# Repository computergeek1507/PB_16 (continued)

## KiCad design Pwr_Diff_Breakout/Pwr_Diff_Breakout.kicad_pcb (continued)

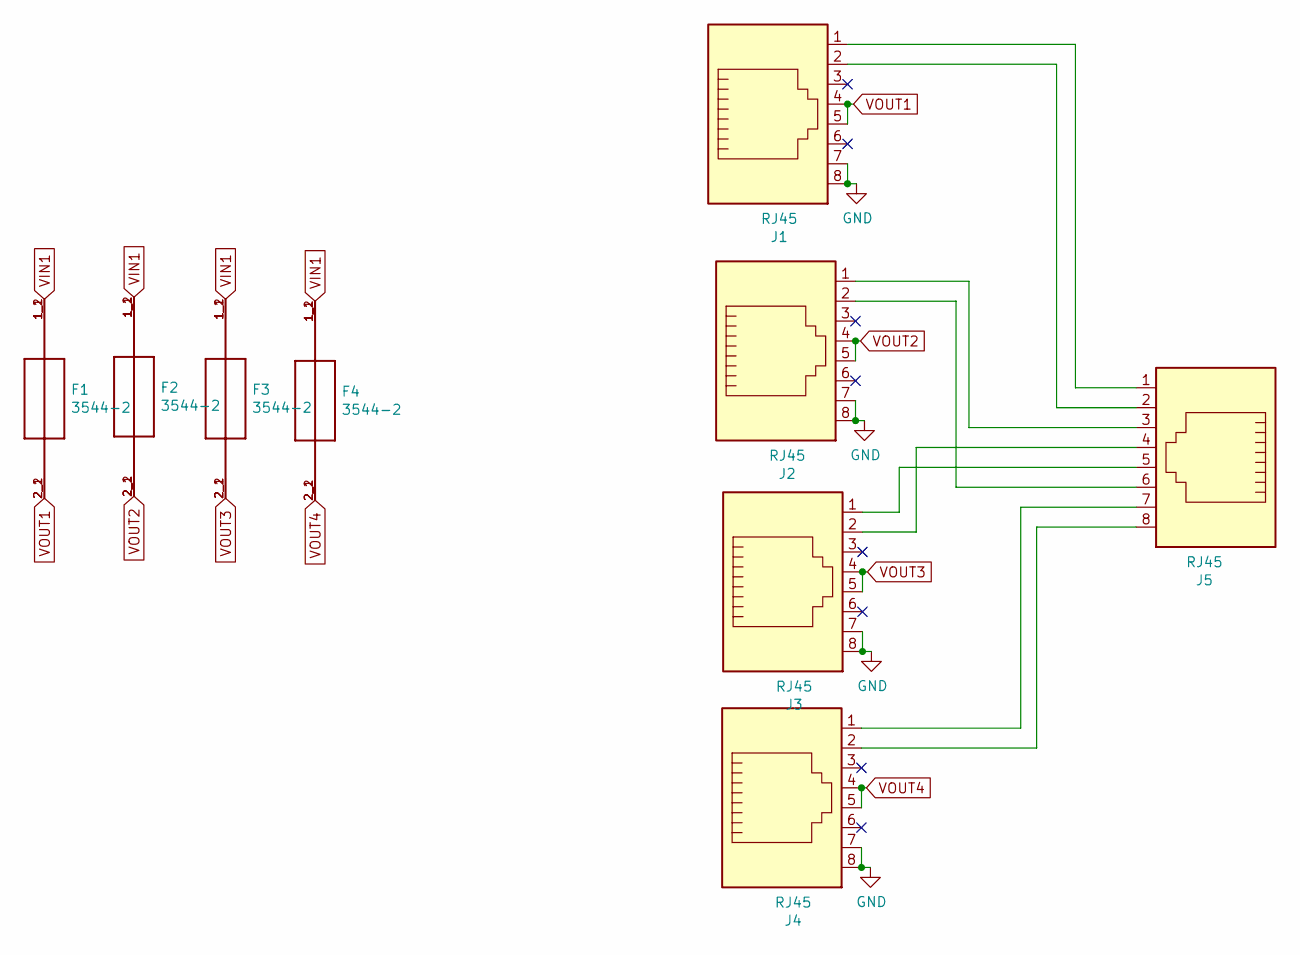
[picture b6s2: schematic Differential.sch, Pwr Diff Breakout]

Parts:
F1, F2, F3, F4: 3544-2; FUSE_3544-2; MPN 3544-2; Digi-Key_PN 36-3544-2-ND
J1, J2, J3, J4, J5: RJ45; RJ45_Amphenol_54602-x08_Horizontal; MPN A-2014-2-4-R; Digi-Key_PN AE10392-ND

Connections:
GND: J1.7, J1.8, J2.7, J2.8, J3.7, J3.8, J4.7, J4.8; also elsewhere on the board
unnamed: J1.1, J5.1
unnamed: J1.2, J5.2
unnamed: J2.1, J5.3
unnamed: J2.2, J5.6
unnamed: J3.1, J5.5
unnamed: J3.2, J5.4
unnamed: J4.1, J5.7
unnamed: J4.2, J5.8
VIN1: F1.1_1 (1), F1.1_2 (1), F2.1_1 (1), F2.1_2 (1), F3.1_1 (1), F3.1_2 (1), F4.1_1 (1), F4.1_2 (1); also elsewhere on the board
VOUT1: F1.2_1 (2), F1.2_2 (2), J1.4, J1.5
VOUT2: F2.2_1 (2), F2.2_2 (2), J2.4, J2.5
VOUT3: F3.2_1 (2), F3.2_2 (2), J3.4, J3.5
VOUT4: F4.2_1 (2), F4.2_2 (2), J4.4, J4.5

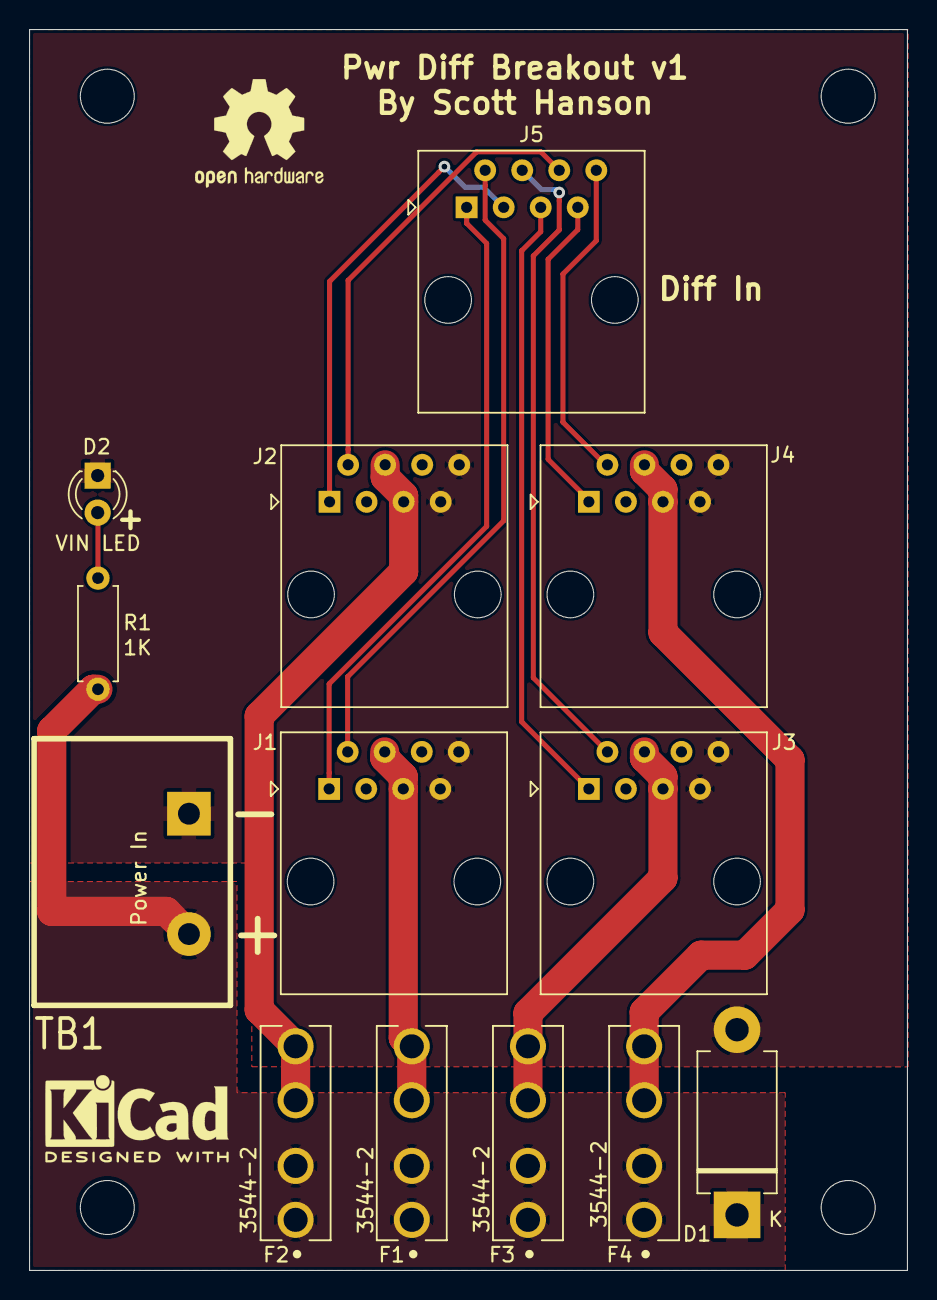
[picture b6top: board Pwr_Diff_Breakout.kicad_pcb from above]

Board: 2 copper layers, 60.2 x 85.1 mm, 13 parts (0 on the bottom side), 15 nets.

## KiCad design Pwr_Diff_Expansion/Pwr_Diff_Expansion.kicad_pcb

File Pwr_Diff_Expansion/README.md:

# Copyright and Disclaimer
Copyright: Scott Hanson

This documentation describes Open Hardware and is licensed under the CERN Open Hardware License Version 2 - Strongly Reciprocal. (CERN-OHL-S)

You may redistribute and modify this documentation under the terms of the CERN OHL-S-v2 (https://ohwr.org/cern_ohl_s_v2.txt). This documentation is distributed WITHOUT ANY EXPRESS OR IMPLIED WARRANTY, INCLUDING OF MERCHANTABILITY, SATISFACTORY QUALITY AND FITNESS FOR A PARTICULAR PURPOSE. Please see the CERN OHL v2-S for applicable conditions

**Under CERN OHL-S-v2, derivative work must be publicly released as defined in subsection 3.3**

# Pwr Diff Expansion

The "Pwr Diff Expansion" board has four single Differental Reciever outputs with power on two CAT5 pins. It works with the "Single_Receiver_Out". All the design files are open source and available on github.

## [Part BOM](https://github.com/computergeek1507/PB_16/raw/master/Pwr_Diff_Expansion/Pwr_Diff_Expansion_BOM.ods)

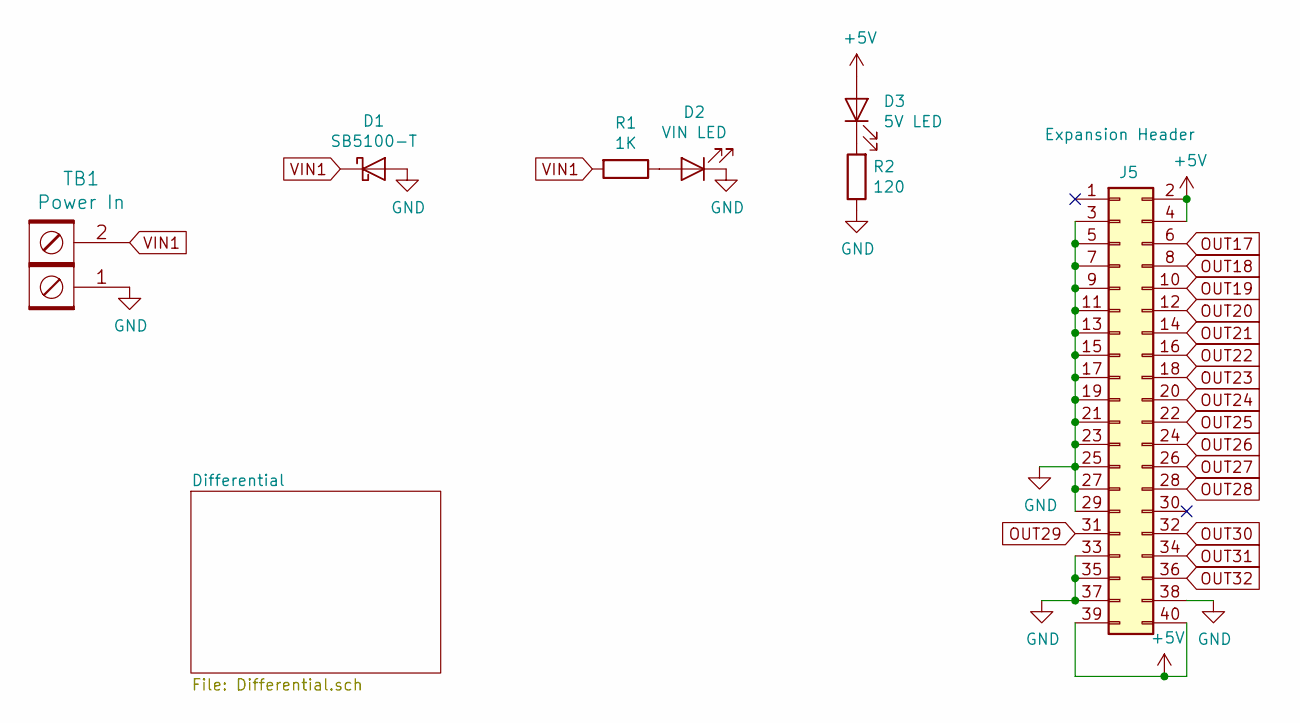
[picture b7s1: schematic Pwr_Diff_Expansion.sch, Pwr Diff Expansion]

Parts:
D1: SB5100-T; D_DO-201AD_P12.70mm_Horizontal; MPN SB5100-T; Digi-Key_PN SB5100DICT-ND
D2: VIN LED; LED_D3.0mm_Clear; MPN WP3A8GD; Digi-Key_PN 754-1217-ND
D3: 5V LED; LED_D3.0mm_Clear; MPN WP3A8GD; Digi-Key_PN 754-1217-ND
J5: Expansion Header; IDC-Header_2x20_P2.54mm_Vertical; MPN SBH11-PBPC-D20-ST-BK; Digi-Key_PN S9175-ND
R1: 1K; R_Axial_DIN0207_L6.3mm_D2.5mm_P7.62mm_Horizontal; MPN CF14JT1K00; Digi-Key_PN CF14JT1K00CT-ND
R2: 120; R_Axial_DIN0207_L6.3mm_D2.5mm_P7.62mm_Horizontal; MPN CF14JT120R; Digi-Key_PN CF14JT120RCT-ND
TB1: Power In; BARRIER_BLOCK_1ROW_2POS_P8.26MM; MPN 4DB-P108-02; Digi-Key_PN A98472-ND

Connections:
+5V: D3.2 (A), J5.2, J5.4, J5.39, J5.40; also elsewhere on the board
GND: D1.2 (A), D2.1 (K), J5.3, J5.5, J5.7, J5.9, J5.11, J5.13, J5.15, J5.17, J5.19, J5.21, J5.23, J5.25, J5.27, J5.29, J5.33, J5.35, J5.37, J5.38, R2.1, TB1.1; also elsewhere on the board
unnamed: D2.2 (A), R1.1
unnamed: D3.1 (K), R2.2
OUT17: J5.6; also elsewhere on the board
OUT18: J5.8; also elsewhere on the board
OUT19: J5.10; also elsewhere on the board
OUT20: J5.12; also elsewhere on the board
OUT21: J5.14
OUT22: J5.16
OUT23: J5.18
OUT24: J5.20
OUT25: J5.22
OUT26: J5.24
OUT27: J5.26
OUT28: J5.28
OUT29: J5.31
OUT30: J5.32
OUT31: J5.34
OUT32: J5.36
VIN1: D1.1 (K), R1.2, TB1.2; also elsewhere on the board

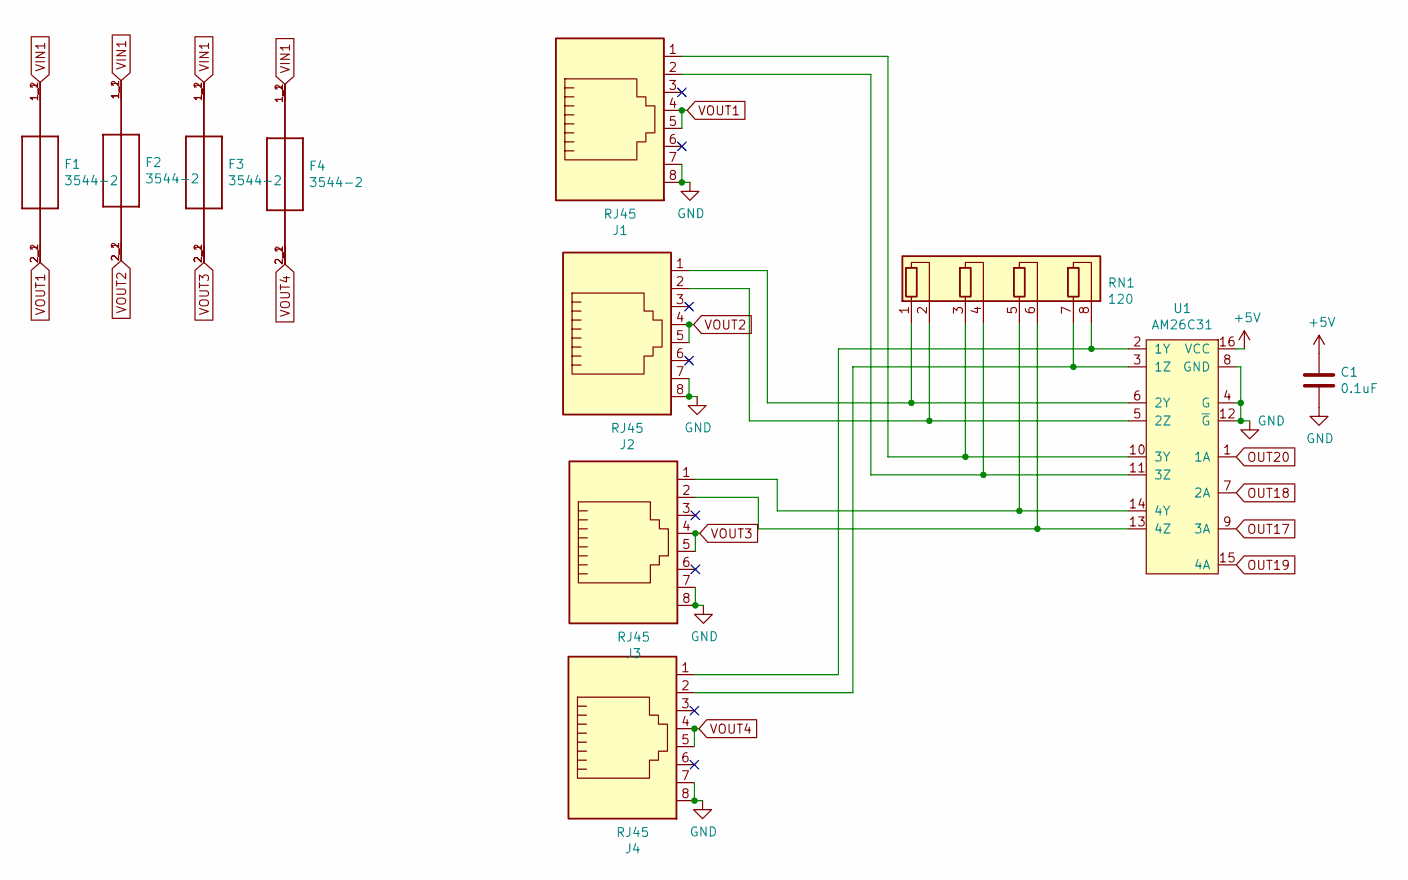
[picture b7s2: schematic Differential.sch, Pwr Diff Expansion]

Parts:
C1: 0.1uF; C_Rect_L7.0mm_W2.0mm_P5.00mm; MPN SR215C104KARTR1; Digi-Key_PN 478-7336-1-ND
F1, F2, F3, F4: 3544-2; FUSE_3544-2; MPN 3544-2; Digi-Key_PN 36-3544-2-ND
J1, J2, J3, J4: RJ45; RJ45_Amphenol_54602-x08_Horizontal; MPN A-2014-2-4-R; Digi-Key_PN AE10392-ND
RN1: 120; R_Array_SIP8; MPN 4608X-102-121LF; Digi-Key_PN 4608X-2-121LF-ND
U1: AM26C31; DIP-16_W7.62mm; MPN AM26C31IN; Farnell 4975637

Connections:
+5V: C1.1, U1.16 (VCC); also elsewhere on the board
GND: C1.2, J1.7, J1.8, J2.7, J2.8, J3.7, J3.8, J4.7, J4.8, U1.4 (G), U1.8 (GND), U1.12 (~G); also elsewhere on the board
unnamed: J1.1, RN1.3 (R2.1), U1.10 (3Y)
unnamed: J1.2, RN1.4 (R2.2), U1.11 (3Z)
unnamed: J2.1, RN1.1 (R1.1), U1.6 (2Y)
unnamed: J2.2, RN1.2 (R1.2), U1.5 (2Z)
unnamed: J3.1, RN1.5 (R3.1), U1.14 (4Y)
unnamed: J3.2, RN1.6 (R3.2), U1.13 (4Z)
unnamed: J4.1, RN1.8 (R4.2), U1.2 (1Y)
unnamed: J4.2, RN1.7 (R4.1), U1.3 (1Z)
OUT17: U1.9 (3A); also elsewhere on the board
OUT18: U1.7 (2A); also elsewhere on the board
OUT19: U1.15 (4A); also elsewhere on the board
OUT20: U1.1 (1A); also elsewhere on the board
VIN1: F1.1_1 (1), F1.1_2 (1), F2.1_1 (1), F2.1_2 (1), F3.1_1 (1), F3.1_2 (1), F4.1_1 (1), F4.1_2 (1); also elsewhere on the board
VOUT1: F1.2_1 (2), F1.2_2 (2), J1.4, J1.5
VOUT2: F2.2_1 (2), F2.2_2 (2), J2.4, J2.5
VOUT3: F3.2_1 (2), F3.2_2 (2), J3.4, J3.5
VOUT4: F4.2_1 (2), F4.2_2 (2), J4.4, J4.5

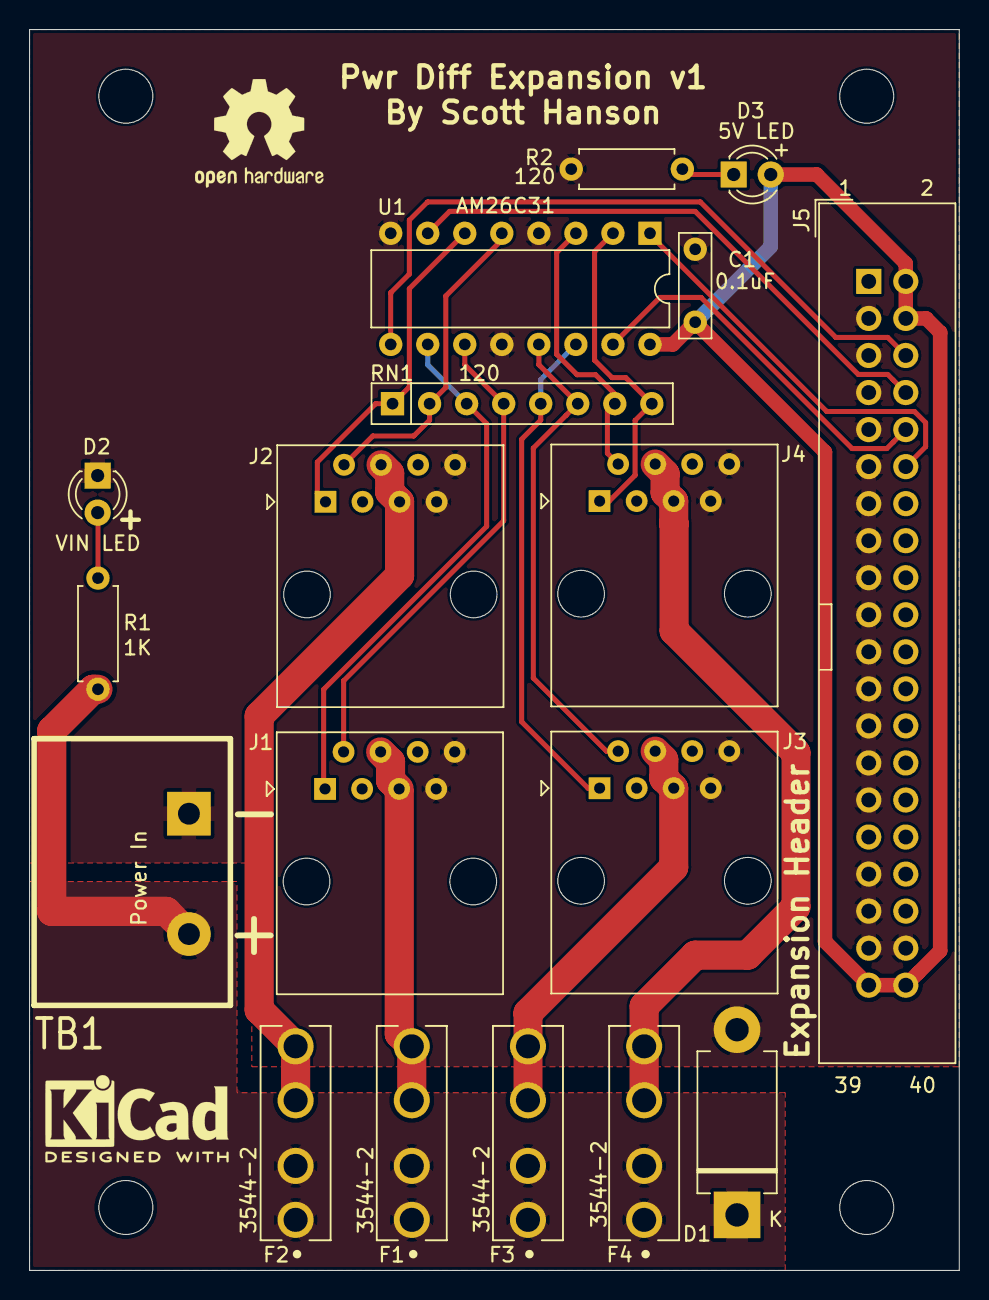
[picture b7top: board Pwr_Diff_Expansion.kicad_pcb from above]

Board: 2 copper layers, 63.8 x 85.1 mm, 18 parts (0 on the bottom side), 21 nets.
